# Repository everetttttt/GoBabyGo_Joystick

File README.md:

# GoBabyGo Joystick Project
### Wichita State University 2024
### Everett Kernen and Jackson Truitt
-----------
-----------

This document aims to help guide GoBabyGo teams through the steps of building a joystick controlled ride-on car. The joystick system was built with this specific model in mind, but could be adapted to other vehicles.

This design is specifically only the electronics and steering components of a GBG build. Any seating adjustments or joystick mounting mechanisms will change for each child and thus must be designed with the individual child in mind.

If you have any questions regarding this project, feel free to open an issue in this repository. I will respond as soon as I can.

## TODO:
 - insert length of carriage bolts and add the links to the BOM
 - create a steering mechanism using a high-torque servo rather than a linear actuator. This would lead to significant savings, as the linear actuator is the single most expensive component other than the car

## Table of Contents
-----------
- [Bill of Materials](#bill-of-materials)
     - [Electronics BOM](#electronics-bom)
     - [Steering mechanism BOM](#steering-assembly-bom)
- [Unpacking the car](#unpacking-your-car-and-components)
- [Preparing the car](#preparing-the-car)
     - [Removal of steering column and motor](#removal-of-steering-column-and-motor)
     - [Removal of steering linkage](#removal-of-steering-linkage)
- [Steering mechanism assembly](#steering-mechanism-assembly)
     - [Steering linkage assembly](#steering-linkage-assembly)
     - [Linear actuator attachment](#linear-actuator-attachment)
     - [Steering linkage installation](#steering-linkage-installation)
     - [Finished steering mechanism](#steering-mechanism-overview)
- [Electronics and programming](#electronics-and-programming)
     - [Preparation](#preparation)
     - [Wiring power](#power)
     - [Power bus and motor controller](#power-bus-and-motor-controller)
     - [PCB preparation](#pcb-preparation)
     - [PCB assembly](#pcb-soldering)
     - [Programming the arduino microcontroller](#programming-the-arduino)
     - **[Parental controls](#parental-controls)**
     - [Testing and fine tuning](#testing-and-fine-tuning)
     - [Finished electronics](#final-engine-bay-appearance)
- [Troubleshooting](#troubleshooting)

## Bill of Materials
-----------
The following tables are lists of all parts required for the electronic and mechanical components of this joystick system. Links and quantities are included.

Quantities are how many per car, not how many packs to purchase. Double check if the link is a multipack.

*Note that if you are at a University and your University has a GBG organization, they may already have many of these components. Check before you purchase. This is particularly true for Wichita State*

**__Vehicle__: [Best Choice Products Kids 12V Ride On Truck, Battery Powered Toy Car w/Spring Suspension, Remote Control, 3 Speeds, LED Lights, Bluetooth - Light Blue](https://www.amazon.com/gp/product/B0C7JK9HNR/ref=ask_ql_qh_dp_hza?th=1)\
This "Jeep" is the one we used and configured the steering mechanism for. Other ride-on vehicles we have seen use extremely similar electronics, so the only difference should be the steering**

### Electronics BOM
| **Item**                         | **Link**                                                                                                                                                           | **Quantity** |   **Additional Notes** | **Item label in case of dead link**   |
| ---                              | ---                                                                                                                                                                | ---          | ---                    | ----                                  |
| Kill Switch                      | [Link](https://www.amazon.com/Toggle-Switches-Rocker-Switch-Waterproof/dp/B07WW3WW3F)                                                                              | 1            | 8 pack | Toggle Switches 8 Pack 2 Pin ON Off SPST Car Rocker Toggle Switches, 20A Heavy Duty Waterproof Toggle Witch
| Arduino Nano Every w/ Headers    | [Link](https://store-usa.arduino.cc/collections/boards-modules/products/arduino-nano-every-with-headers)                                                           | 1            | Microcontroller, brains of the operation | Arduino Nano Every with Headers
| Motor Controller                 | [Link](https://www.amazon.com/HOBBYWING-QUICRUN-Waterproof-Brushed-Motors/dp/B07NYBF6MQ)                                                                           | 1            | | HOBBYWING QUICRUN 880 ESC, Waterproof ESC for Dual Brushed Motors
| Motor Controller Programmer      | [Link](https://www.hobbywingdirect.com/products/led-pc2c?variant=172030922)                                                                                        | 1            | Only one is ever needed for a GBG org. Check to see if you have one already | HOBBYWING LED Program Card
| Joystick                         | [Link](https://www.amazon.com/Acxico-Joystick-Potentiometer-JH-D202X-R2-Thermistor/dp/B09JZ8ZV4L)                                                                  | 1            | | Acxico 1Pcs Joystick Potentiometer JH-D202X-R2/R4 5K 10K ohm 2-axis Sealed PTZ Thermistor
| RC Controller                    | [Link](https://www.amazon.com/DUMBORC-Transmitter-Receiver-Controller-400m-500m/dp/B07RR81GSB)                                                                     | 1            | used for parental override over the joystick controls | X4 4CH RC Radio System Transmitter and Receiver X6F 2.4ghz Remote Controller for RC Car Boat Tanks(Distance 400m-500m) Controller Transmitter
| 30A bus bar                      | [Link](https://www.amazon.com/OONO-Position-Terminal-Distribution-Module/dp/B09D3BV22M)                                                                            | 1            | Power distribution | OONO 30Amp 48V 2x6 Position Terminal Block Distribution Module 
| 4ft servo wires                  | [Link](https://www.readymaderc.com/products/details/120cm-48in-jr-twisted-22awg-servo-cable?srsltid=AfmBOooBtGZkchE-u-FVPZSh1Mha9t9dLRYeGN2BnarDRjaqf-3A2QVKya4)   | 3            | Connect the joystick to the arduino through the car, so lots of length is good | 120cm (48 inch) JR Style 22AWG Twisted Servo Extension Cable
| Speed control potentiometers     | [Link](https://www.amazon.com/Uxcell-a15040700ux0380-Terminals-Linear-Potentiometer/dp/B019I13X5K)                                                                 | 1            | | uxcell 5pcs 10K OHM 3 Terminal Linear Taper Rotary Audio B Type Potentiometer Height 36cm 
| Steering control potentiometers  | [Link](https://www.digikey.com/en/products/detail/bourns-inc/3296W-1-103LF/1088045)                                                                                | 2            | Dial in steering center and range | Bourns 3296W-1-103LF
| 15 pin female header pins        | [Link](https://www.amazon.com/2-54mm-Female-Single-Straight-Header/dp/B07VP63Z78)                                                                                  | 2            | Connect the arduino to the PCB | 10 pcs. 15 Pin 2.54mm Pitch 15 Pin Female Single Row Straight Header Strip PH:8.5mm 
| Male header pins                 | [Link](https://www.amazon.com/HiLetgo-20pcs-2-54mm-Single-Header/dp/B07R5QDL8D)                                                                                    | 1            | Connect everything else to the PCB. You'll break them off in 3 pin chunks, of which you'll need 7. 21 pins total | HiLetgo 20pcs 40P 2.54mm Pitch Single Row Pin Header Strip 40Pin 2.54mm Pitch 
| Spade connectors                 | [Link](https://www.amazon.com/Connectors-Shrink-Terminals-Female-MENTBERY/dp/B0BFDJNK91?source=ps-sl-shoppingads-lpcontext&ref_=fplfs&smid=A2TBO4E1CS6T20&th=1)    | 4            | Connect the motor controller wires to the motor wires. | 150 PCS Spade Connectors, Heat Shrink Spade Terminals 22-10 AWG, Wire Connectors Male and Female by MENTBERY 
| PCB                              | none                                                                                                                                                               | 1            | See notes below | See notes below

*You will also need access to a soldering iron and a couple feet of 14AWG wire*

### Steering Assembly BOM
| **Item**                              | **Link**                                                                                          | **Quantity** | **Additional Notes**   |
| ---                                   | ---                                                                                               | ---          | ---                    |
| Linear Actuator (part 13)             | [Link](https://www.servocity.com/4-stroke-25-lb-thrust-linear-servo/)                             | 1 | Heavy-Duty Linear Servo (Position Control, 12-24V, 33lb Thrust, 1.7"/sec, 4" Stroke). Used for steering. At $300, this is by far the biggest opportunity to reduce costs. Unfortunately, we did not have time to test cheaper options, like [this servo](https://www.amazon.com/GoolRC-Digital-Torque-Waterproof-Replacements/dp/B0B5H4MWZG)
| Mounting bracket (part 4)             | [Link](https://www.servocity.com/universal-mounting-bracket-for-heavy-duty-linear-actuator/)      | 1 | Universal Mounting Bracket for Heavy-Duty Linear Actuator
| 1" square aluminum tube               |                                                                                                   |   |                                   |
| 5" Threaded rod end bolt (part 5)     | [Link](https://www.mcmaster.com/2440K41/)                                                         | 1 | High-Strength Fully Threaded Rod End Bolt. 3/8"-16 shank thread, 5" shank length
| 4" Threaded rod end bolt (part 6)     | [Link](https://www.mcmaster.com/2440K78/)                                                         | 1 | High-Strength Fully Threaded Rod End Bolt. 3/8"-16 shank thread, 4" shank length
| Internal threaded rod (part 7)        | [Link](https://www.mcmaster.com/7417N87/)                                                         | 1 | Internally Threaded Connecting Rod. 18-8 Stainless Steel, 3/8"-16 thread, 12" length
| 3/8" Shoulder screw (part 8)          | [Link](https://www.mcmaster.com/91259A481/)                                                       | 1 | Alloy Steel Shoulder Screw. 3/8" shoulder diameter, 7/16" shoulder length, 5/16"-18 thread
| 5/16 Shoulder screw (part 15)         | [Link](https://www.mcmaster.com/91273A183/)                                                       | 1 | Same-Size Thread 18-8 Stainless Steel Shoulder Screew. 5/16" shoulder diameter, 3" shoulder length, 5/16"-18 thread
| 3/8" Washer (part 9)                  | [Link](https://www.mcmaster.com/92141A031/)                                                       | 1 | 18-8 Stainless Steel Washer. For 3/8" screw size. 0.875" outer diameter
| 5/16" Washer (part 12)                | [Link](https://www.mcmaster.com/92141A030/)                                                       | 2 | 18-8 Stainless Steel Washer. For 5/16" screw size. 0.75" outer diameter
| Hex Nut (part 10)                     | [Link](https://www.mcmaster.com/95462A031/)                                                       | 2 | Medium-Strength Steel Hex Nut. Grade 5, Zinc-plated. 3/8"-16 thread
| Locking Hex Nut (part 11)             | [Link](https://www.mcmaster.com/95615A160/)                                                       | 2 | Medium-Strength Steel Nylon-Insert Locknut. Grade 5, Zinc-plated. 5/16"-18 thread
| 1.75" Aluminum Spacer (part 16)       | [Link](https://www.mcmaster.com/92511A108/)                                                       | 1 | Aluminum Unthreaded Spacer. For 5/16" screw size. 1.75" length. 0.75" outer diameter

* PCB
     - You can upload the attached [gerber file](/GBG_Joystick_PCB_v4.zip) to a PCB manufacturer of your choice (PCBWay, JLCPCB, among others). You can also see and modify the [KiCAD files](/KiCAD/) and export from there.
     - Alternatively, you could build this on a breadboard or solder all wires together. If you do that, I highly recommend you reference the [schematic](/KiCAD/KiCAD.kicad_sch).

## Unpacking your car and components
-----------
- Once you get your vehicle, unpack the car and inspect it to ensure all the pieces are present and there is no damage to the vehicle
- Sort the componets, both electrical and mechanical, into two areas according to the BOM
- You don't need to assemble the vehicle at this point, as several components will be removed

## Preparing the car 
-----------

### Removal of steering column and motor

1. Using a hammer and punch, push out the silver pin on top of the steering column that holds the steering wheel adapter to the steering column. The pin should come out with medium force

2. With the pin removed, the black cap that held the pin in should be able to be removed easily by pulling it up and away from the vehicle. This will leave a hole in the dashboard

3. Now that the pin and black retaining cap are removed, drop the steering column (circled in blue) out of the vehicle through the bottom

4. Remove the gearbox from the bottom of the vehicle by first unplugging it from the existing car controller, then dropping it out of the vehicle. The bottom of the car should now look like the following photo

5. Following the manufacturers instructions, install the front steering axle and suspension. The bottom of the car should end up like the following

### Removal of steering linkage

1. The steering linkage (circled in yellow) that connects the right and left front wheel mounts needs to be removed. To do this, the pins that connect the linkage (circled in blue) should be drilled out

2. Using a 5/16" drill bit, slowly drill the pins out. When complete, the linkage will be disconnected as shown below. 
     - *Note: drill slowly with light to medium pressure and use cutting oil to ensure you don't damage or break the drill bit. You may need to hold the pin using pliers to ensure it does not slip and rotate during drilling*

## Steering mechanism assembly
-----------

During this process, please reference the final assembly and exploded view below. You may also reference the assembly video [here](https://www.youtube.com/watch?v=7GvAFjcBryw)

### Steering linkage assembly
1. Thread one hex nut (part 10) onto each of the threaded rod end bolts (parts 5 and 6) about 0.875 inches

2. Take the internal threaded rod (part 7) and screw the bolts into each side until the rod touches the nuts. Then, tighten each nut into the rod to create jam nuts

### Linear actuator attachment
1. Cut a piece of 1" square tubing to the length of the mounting bracket (part 4). This should be about 1.7 inches
2. Copy the location of the holes on the mounting bracket to the square tube, then drill those holes using a 5/16" drill bit
3. Scribe a line 7 inches from the left axle bar
4. Align the mounting bracket to this scribe line and mark the holes, then drill those holes using a 5/16" drill bit
5. Using **insert length here** 5/16" carriage bolts, mount the linear actuator mount to the car with the 1" aluminum square tube between the mount and vehicle crossbar
6. Using the supplied pin and retaining clip, mount the Linear Actuator (part 13) to the mounting bracket as shown below. The linear actuator should face to the vehicle's left side.

### Steering linkage installation
**Note: do a dry fit before using the locking nut to confirm the distance between wheels is correct and the wheels will be aligned properly after installation. To change the length, simply screw/unscrew the connecting rod ends and re-tighten the jam nut.** 
1. On the side opposite the linear actuator, install the following in order from bottom to top
     - 3/8" shoulder screw (part 8)
     - 3/8" washer (part 9)
     - 5" connecting rod end (part 5)
     - Vehicle steering carriage
     - 3/8" washer (part 9)
     - 5/16" locking nut (part 11)

2. On the side nearest the linear actuator, install the following in order from bottom to top
     - 5/16" shoulder screw (part 15)
     - 4" connecting rod end (part 6)
     - Vehicle steering carriage
     - 5/16", 1.75" aluminum spacer (part 16)
     - 3/8" washer (part 9)
     - Linear actuator (part 13)
     - 5/16" locking nut (part 11)

## Steering mechanism overview
At this point, the steering mechanism should be fully installed as shown in the picture below. You may need to drill a hole in the front of the "engine bay" to run the linear actuator wires.

## Electronics and programming
-----------

The code to upload to the Arduino is in the Arduino folder

**PCB information**
- You can upload `GBG_Joystick_PCB_v4.zip` to a PCB manufacturer of your choice (PCBWay, JLCPCB, DKRed, among others) to get multiple PCBs printed for reasonably cheap.
- If you want to modify the PCB or schematic, all the KiCAD files are in the KiCAD folder
- Alternatively, you could build this on a breadboard or solder. In that case, you can reference the schematic either in KiCAD or in the [images folder](images/_Schematic.png)

### Preparation
1. After assembling your vehicle, the "engine bay" will look like the following. It looks like (and is) a jumbled mess of wires, but the components relevant to us are outlined.

2. Before doing anything, disconnect the battery, wires outlined in yellow
3. Double check you've disconnected the battery
3. Disconnect the green connector. It leads to the motors which power the car
4. Disconnect the steering motor, if you did not already do so in the steering mechanism assembly. The wires are typically blue and brown.

### Power
1. Cut a small board to place your components on. You could use MDF or cardboard
2. Gather your 30A bus, a spool of wire (14-18AWG), and your kill switch
3. Cut the orange wires about three inches from the connector. Again, make sure it is not connected to the battery
4. Strip all four wires about a quarter of an inch
5. Take the red wire on the orange connector side and crimp on a spade connector that fits the wire gauge. Once crimped, pull to ensure security
6. From your 14-18AWG spool of wire, strip the same amount from two wires and crimp the opposite spade connector on one, then connect the two spade connectors together
7. Run both wires to the rear of the car, running the wire along the bottom or side of the car to keep things tidy
8. Use wire nuts or spade connectors to connect the two wires to your kill switch
9. Use a drill and the accompanying nuts that came with the switch to attach it securely to the rear of the car

10. Take your 30A bus and screw into block A the remaining wire from the kill switch connection, and into block B the black wire from the orange connector
11. Run the linear actuator power wires into the "engine bay," then screw red into A and black into B

*Note that the motor controller here is what powers the arduino and PCB. It will act as our voltage regulator, giving the arduino a clean 5 volts*

### Power bus and motor controller
1. Ensure the battery remains disconnected, if you connected it to test kill switch continuity
2. Connect the wires previously connected to the orange connector into the 30A bus, with red going to A and black going to B
3. Cut and strip the red and black power wires from your motor controller and screw red into A, black into B
4. Cut and strip one blue wire and one yellow wire, then crimp on spade connectors. Use the same spade connector for both
5. Cut and strip the two wires leading to the rear motors. In the picture before, this connector is outlined in green. Crimp the opposite spade connector onto both
6. Connect the blue/yellow wires and the motor wires. Don't worry about if they're backwards, you can just swap them later when we test if so

*Note that the motor controller may come with the proper configuration to power the rear motors. If not, connect it to the Motor Controller Programmer and follow the instructions there to program your motor controller as desired*

### PCB preparation
First, we need to solder pins to the joystick. You may have noticed we specified 4 servo wires in the BOM - we will be soldering two of those wires to the joystick, then the other two wires will connect those wires to the PCB\
This is easily the most difficult soldering job in this project, so be prepared. If you haven't soldered before, consider asking for help or advice
1. Grab the joystick and two servo wires. Cut the wires about two inches above the female connector, then strip about 1/8"
2. Drop a small piece of heat-shrink tubing over each of the 6 individual wires, then solder each wire to the joystick leads
3. Move the heat shrink tubing over the solders and shrink them into place, protecting the solder joints and preventing them from shorting to each other

*Don't worry about the orientation. We can just turn the wires around when connecting to the PCB if necessary*

### PCB soldering
This part of the soldering should be significantly easier, as all components will slot in
1. Gather your PCB, two 15-pin female headers, seven 3-pin male headers, and all three potentiometers

2. Solder all components from the underside. When soldering the 15-pin headers, we recommend putting the arduino into the headers to ensure the two headers stay aligned

3. Plug all components into the PCB!

### Programming the arduino
1. Open the [Arduino sketch](/Arduino/Arduino.ino) in the [Arduino IDE](https://www.arduino.cc/en/software) on a computer
2. Connect the arduino to your computer via a USB cable, then flash the program to the arduino

### Parental controls
Parental controls are achieved via an RC controller. The controller sends instructions to the arduino microcontroller, which then override any input from the joystick.

There are three controls available to parents. 
1. The trigger will move the car forward or backward and will override forward/backward input from the joystick. It will __not__ override steering from the joystick unless the RC wheel is also turned
2. The wheel will steer the car and override left/right input from the joystick. It will __not__ override forward/backward input from the joystick unless the RC trigger is also activated
3. The blue button on the RC handle is an Emergency Stop. It will prevent the car from accepting any input from either the joystick or RC controller

*Note that this project also includes a kill switch that will shut the car down, if within arm's reach or when storing. The kill switch is functionally equivalent to unplugging the battery*

To set up the RC controls, grab the RC receiver and place it near the PCB. Tape the antenna where there will be little interference. Run jumper wires from the receiver to the PCB according to this diagram

### Testing and fine tuning
1. Use the 4 foot extension wires to connect the joystick to the PCB. Plug the battery in and flip the kill switch on
2. If nothing looks amiss, turn the joystick in all directions. Turn the joystick in your hand until the directions are correct. If one of two axes are flipped, simply unplug the connector from the PCB and turn it around
3. The vehicle should now have steering and motors functional
4. To increase or reduce speed, turn the speed potentiometer until you are satisfied. Turned all the way to the right will give speed equivalent to how it arrived, turning counterclockwise will reduce the top speed
5. Next, flip the car over or get into a position you can see the steering. It is likely not centered or has too wide/narrow a steering range. To fix this, turn the steering center and range adjustment potentiometers with a small screwdriver and test by moving the joystick in both directions to ensure it does not hit anything in the wheel bay and returns to center as expected
6. Finally, test the RC controller. Ensure the trigger, wheel, and emergency stops work as intended. If it has a different range or center than the joystick, open the top flap and adjust the knobs until they are equivalent

### Final engine bay appearance
- Power comes out of the battery positive terminal (red wire), through the blue wire nut and out to the kill switch, returning to the 30A bus side A.
- From there, power goes out to the motor controller and the linear actuator (ignore the extraneous wires leaving the frame in the bottom left)
- The motor controller sends power to the rear motors via the blue and yellow wires connecting through the spade connectors. Two wires are left unconnected. The motor controller both powers the arduino and is controlled by it
- The arduino receives power from the motor controller and, receiving signals from the configuration potentiometers, joystick, and RC receiver, controls the motors and linear actuator through servo wires

## Troubleshooting
If the car does not move when turned on, check that the RC controller is on. Occasionally, the RC receiver may, on start, send a signal that the Emergency Stop is on. Turning the controller on sends the proper signal to the receiver

Ensure all components are fully seated into their connectors

Ensure the solder joints on the PCB make a proper connection.

If none of these work or if the vehicle motors/steering is wonky, connect the arduino to your computer and read the Serial Monitor. Check that the values there match up generally to what's written in the code. If you have trouble parsing the code, please feel free to open an issue in this github repo.

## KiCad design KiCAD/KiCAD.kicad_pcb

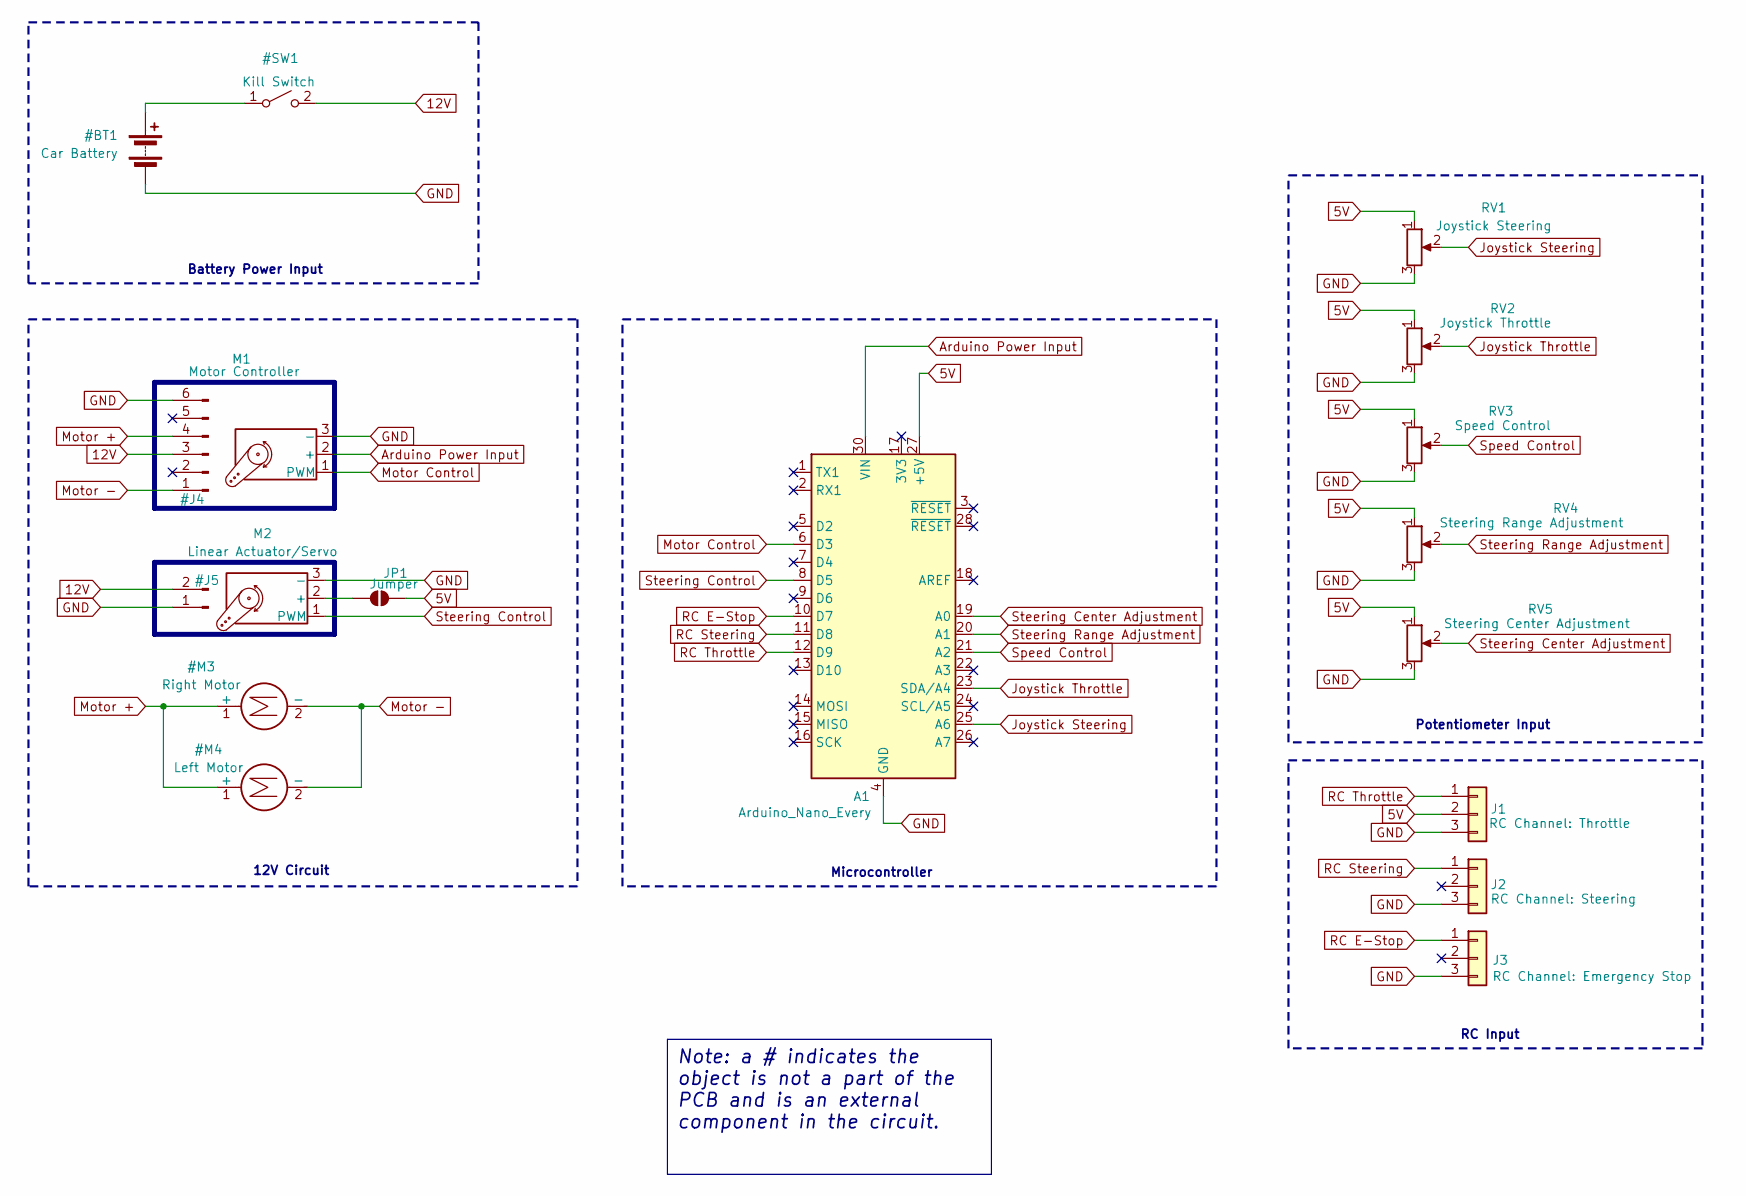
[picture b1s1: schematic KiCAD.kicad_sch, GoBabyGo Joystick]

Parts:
A1: Arduino_Nano_Every; Arduino_Nano
J1: RC Channel: Throttle; PinHeader_1x03_P2.54mm_Vertical
J2: RC Channel: Steering; PinHeader_1x03_P2.54mm_Vertical
J3: RC Channel: Emergency Stop; PinHeader_1x03_P2.54mm_Vertical
JP1: Jumper; SolderJumper-2_P1.3mm_Open_Pad1.0x1.5mm
M1: Motor Controller; PinHeader_1x03_P2.54mm_Vertical
M2: Linear Actuator/Servo; PinHeader_1x03_P2.54mm_Vertical
RV1: Joystick Steering; PinSocket_1x03_P2.54mm_Vertical
RV2: Joystick Throttle; PinSocket_1x03_P2.54mm_Vertical
RV3: Speed Control; PinHeader_1x05_P2.54mm_Vertical
RV4: Steering Range Adjustment; Potentiometer_Vishay_T93YA_Vertical
RV5: Steering Center Adjustment; Potentiometer_Vishay_T93YA_Vertical

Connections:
5V: A1.27 (+5V), J1.2, JP1.2 (B), RV1.1, RV2.1, RV3.1, RV4.1, RV5.1
Arduino Power Input: A1.30 (VIN), M1.2 (+)
GND: A1.4 (GND), A1.29 (GND), J1.3, J2.3, J3.3, M1.3 (-), M2.3 (-), RV1.3, RV2.3, RV3.3, RV4.3, RV5.3
Joystick Steering: A1.25 (A6), RV1.2
Joystick Throttle: A1.23 (SDA/A4), RV2.2
Motor Control: A1.6 (D3), M1.1 (PWM)
unnamed: JP1.1 (A), M2.2 (+)
RC E-Stop: A1.10 (D7), J3.1
RC Steering: A1.11 (D8), J2.1
RC Throttle: A1.12 (D9), J1.1
Speed Control: A1.21 (A2), RV3.2
Steering Center Adjustment: A1.19 (A0), RV5.2
Steering Control: A1.8 (D5), M2.1 (PWM)
Steering Range Adjustment: A1.20 (A1), RV4.2

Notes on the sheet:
Battery Power Input
Potentiometer Input
12V Circuit
RC Input
Microcontroller
Note: a # indicates the object is not a part of the PCB and is an external component in the circuit.

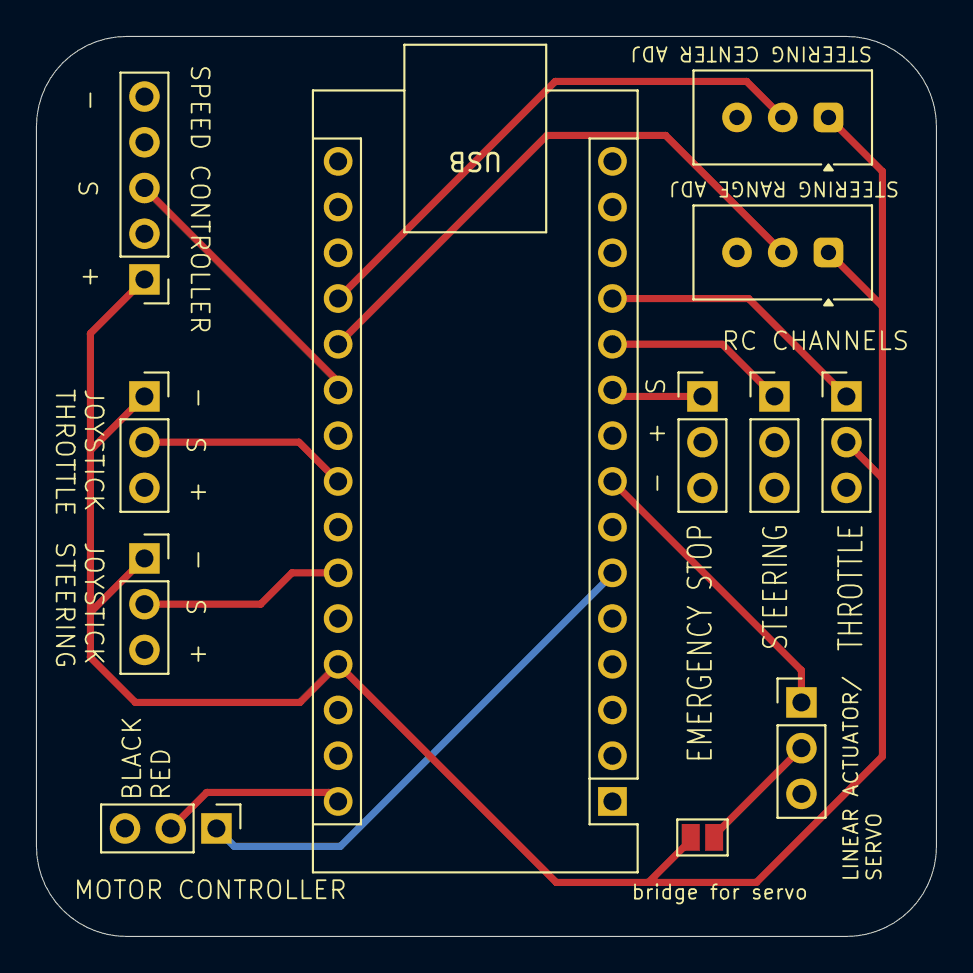
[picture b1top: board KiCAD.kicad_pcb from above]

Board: 2 copper layers, 50.0 x 50.0 mm, 12 parts (0 on the bottom side), 14 nets.

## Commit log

2024-01-24 Adding previously working arduino code and a test template for seeing what the linear actuator will output
2024-01-24 added wiring diagram for previous working version (no linear actuator)
2024-02-13 moved file
2024-02-13 added nano every pinout so I don't have to google it every time
2024-02-13 added motor controller test
2024-04-10 updated email and added wiring diagram from previous year
2024-04-10 fully rewrote arduino file for pcb and using servo controls for both motors and steering
2024-04-10 comment added to todo
2024-04-15 added previous gbg code and added pwm to new code
2024-04-15 mostly finished code, testing later today
2024-04-15 quick comment
2024-04-15 added pcb gerber file
2024-04-15 new pcb
2024-04-16 committing before combining if statements
2024-04-16 working all-in-one pwm signal
2024-04-16 fixed steering and removed rc capability for now
2024-04-16 RC inputs
2024-04-18 cleaned up and moved files around, replaced PCB gerber v2 with the final v4
2024-04-23 updated code w adjustments and in person testing
2024-04-23 updated code, not sure why it doesn't work
2024-04-30 working, just don't have full override on rc
2024-04-30 full working joystick and rc controls
2024-08-19 Added KiCAD files and documentation photos
2024-08-20 Renamed arduino script and removed old wiring diagrams
2024-08-20 Remade KiCAD files
2024-08-20 Wrote README and added images
2024-08-20 Updated README and added images
2024-08-20 Fixed assembled PCB image
2025-07-12 photo rename, readme update
2025-07-12 update photos and readme
